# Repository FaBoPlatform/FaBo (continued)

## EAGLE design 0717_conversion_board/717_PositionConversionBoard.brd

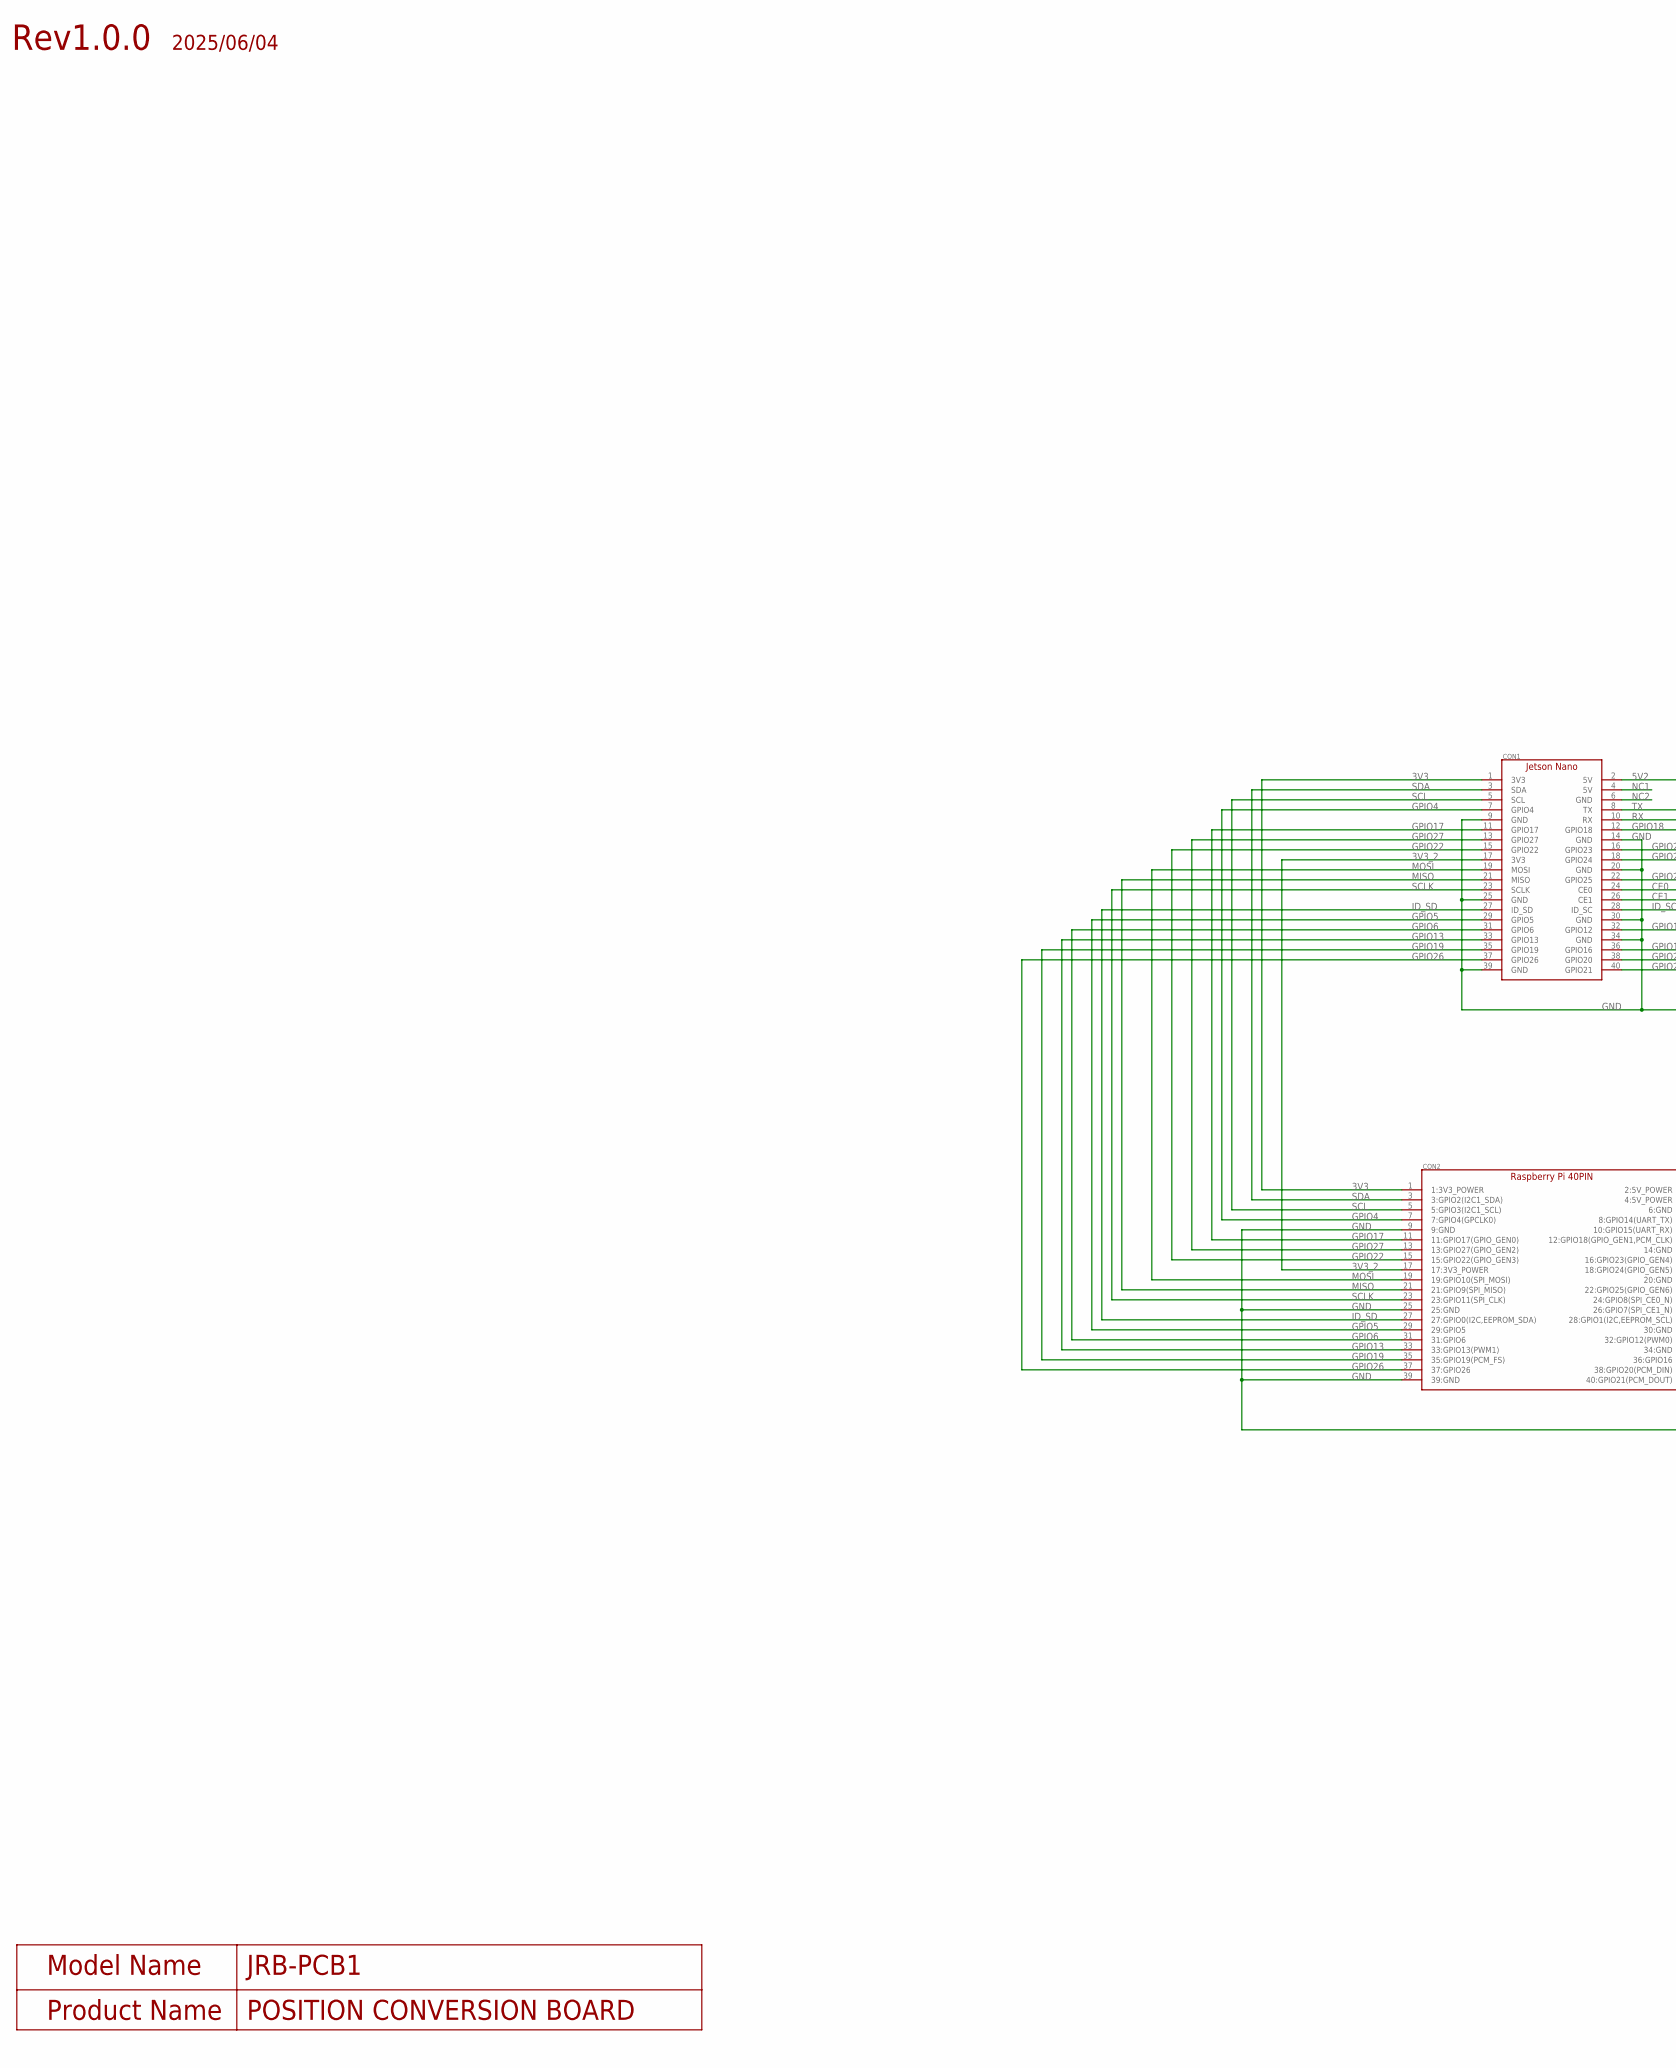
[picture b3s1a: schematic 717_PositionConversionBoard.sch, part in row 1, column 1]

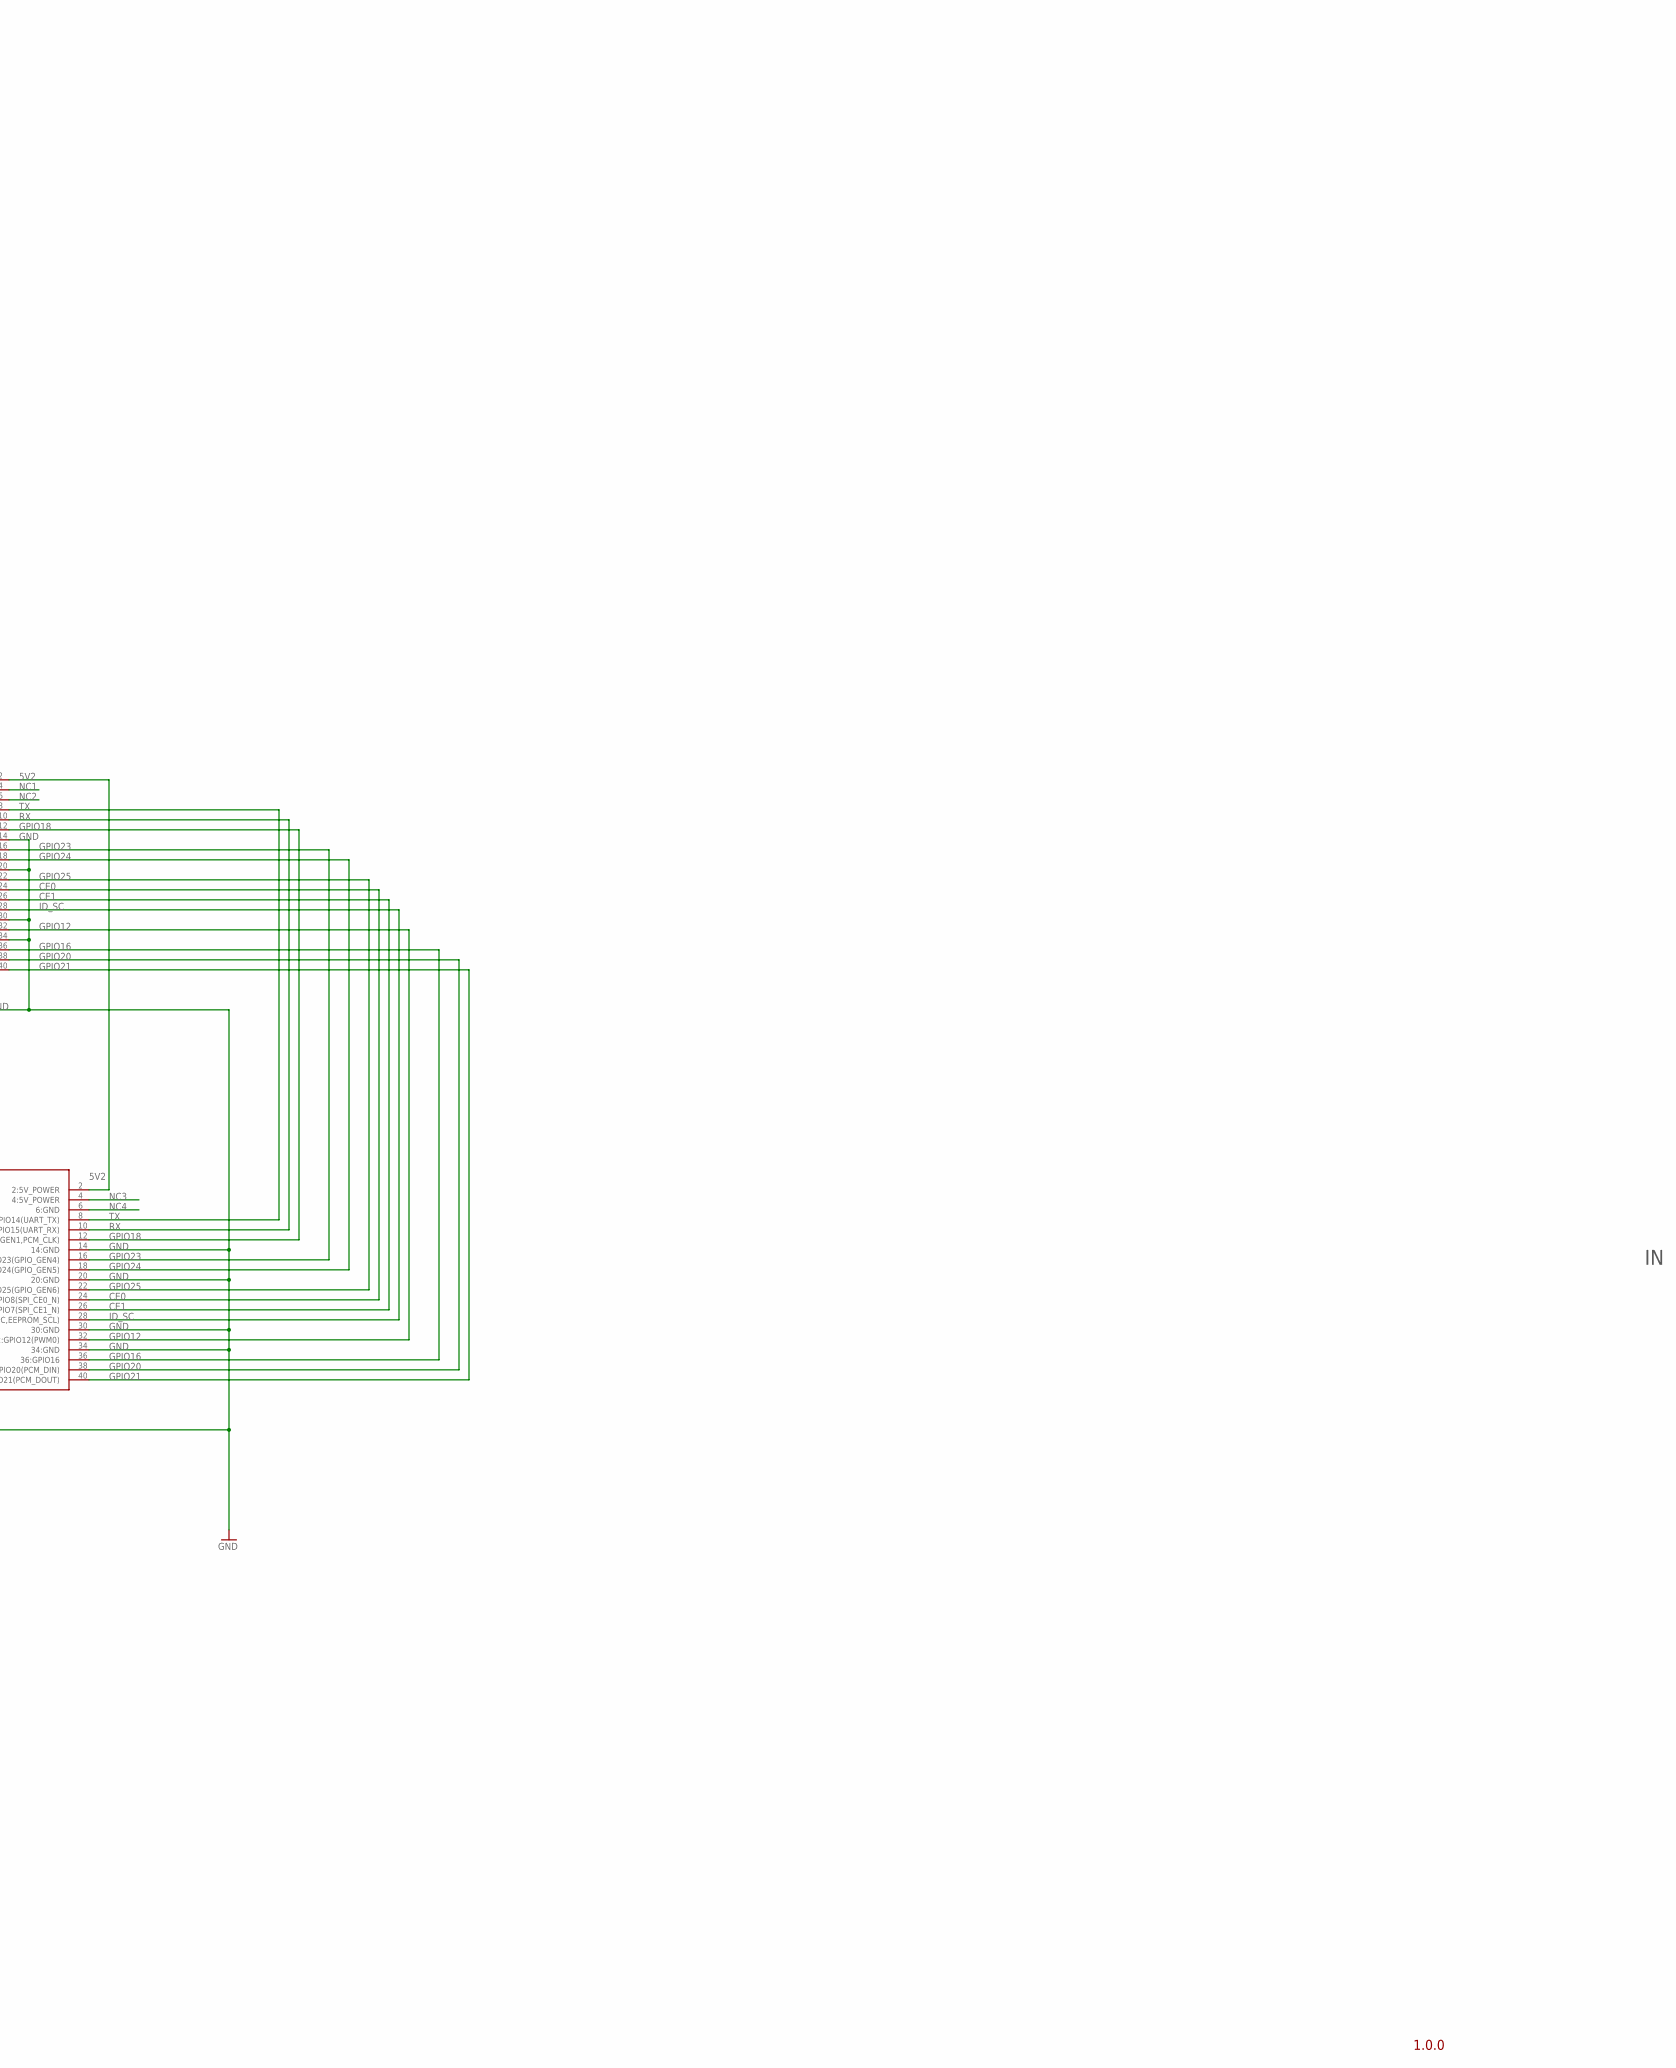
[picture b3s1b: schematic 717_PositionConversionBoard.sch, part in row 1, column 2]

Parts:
CON1: JETSON_NANOJETSON_ORIN_NANO; JETSON_ORIN_NANO_DIMENTION
CON2: RASPBERRYPI_SHEILDUPPERBOARD; RASPBERRY_PI_SHILED_NONDEMETION

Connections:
3V3: CON1.1 (3V3), CON2.1 (1:3V3_POWER)
3V3_2: CON1.17 (3V3), CON2.17 (17:3V3_POWER)
5V2: CON1.2 (5V), CON2.2 (2:5V_POWER)
CE0: CON1.24 (CE0), CON2.24 (24:GPIO8(SPI_CE0_N))
CE1: CON1.26 (CE1), CON2.26 (26:GPIO7(SPI_CE1_N))
GND: CON1.9 (GND), CON1.14 (GND), CON1.20 (GND), CON1.25 (GND), CON1.30 (GND), CON1.34 (GND), CON1.39 (GND), CON2.9 (9:GND), CON2.14 (14:GND), CON2.20 (20:GND), CON2.25 (25:GND), CON2.30 (30:GND), CON2.34 (34:GND), CON2.39 (39:GND)
GPIO4: CON1.7 (GPIO4), CON2.7 (7:GPIO4(GPCLK0))
GPIO5: CON1.29 (GPIO5), CON2.29 (29:GPIO5)
GPIO6: CON1.31 (GPIO6), CON2.31 (31:GPIO6)
GPIO12: CON1.32 (GPIO12), CON2.32 (32:GPIO12(PWM0))
GPIO13: CON1.33 (GPIO13), CON2.33 (33:GPIO13(PWM1))
GPIO16: CON1.36 (GPIO16), CON2.36 (36:GPIO16)
GPIO17: CON1.11 (GPIO17), CON2.11 (11:GPIO17(GPIO_GEN0))
GPIO18: CON1.12 (GPIO18), CON2.12 (12:GPIO18(GPIO_GEN1,PCM_CLK))
GPIO19: CON1.35 (GPIO19), CON2.35 (35:GPIO19(PCM_FS))
GPIO20: CON1.38 (GPIO20), CON2.38 (38:GPIO20(PCM_DIN))
GPIO21: CON1.40 (GPIO21), CON2.40 (40:GPIO21(PCM_DOUT))
GPIO22: CON1.15 (GPIO22), CON2.15 (15:GPIO22(GPIO_GEN3))
GPIO23: CON1.16 (GPIO23), CON2.16 (16:GPIO23(GPIO_GEN4))
GPIO24: CON1.18 (GPIO24), CON2.18 (18:GPIO24(GPIO_GEN5))
GPIO25: CON1.22 (GPIO25), CON2.22 (22:GPIO25(GPIO_GEN6))
GPIO26: CON1.37 (GPIO26), CON2.37 (37:GPIO26)
GPIO27: CON1.13 (GPIO27), CON2.13 (13:GPIO27(GPIO_GEN2))
ID_SC: CON1.28 (ID_SC), CON2.28 (28:GPIO1(I2C,EEPROM_SCL))
ID_SD: CON1.27 (ID_SD), CON2.27 (27:GPIO0(I2C,EEPROM_SDA))
MISO: CON1.21 (MISO), CON2.21 (21:GPIO9(SPI_MISO))
MOSI: CON1.19 (MOSI), CON2.19 (19:GPIO10(SPI_MOSI))
NC1: CON1.4 (5V)
NC2: CON1.6 (GND)
NC3: CON2.4 (4:5V_POWER)
NC4: CON2.6 (6:GND)
RX: CON1.10 (RX), CON2.10 (10:GPIO15(UART_RX))
SCL: CON1.5 (SCL), CON2.5 (5:GPIO3(I2C1_SCL))
SCLK: CON1.23 (SCLK), CON2.23 (23:GPIO11(SPI_CLK))
SDA: CON1.3 (SDA), CON2.3 (3:GPIO2(I2C1_SDA))
TX: CON1.8 (TX), CON2.8 (8:GPIO14(UART_TX))

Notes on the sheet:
1.0.0
Rev1.0.0
2025/06/04
Model Name
JRB-PCB1
Product Name
POSITION CONVERSION BOARD

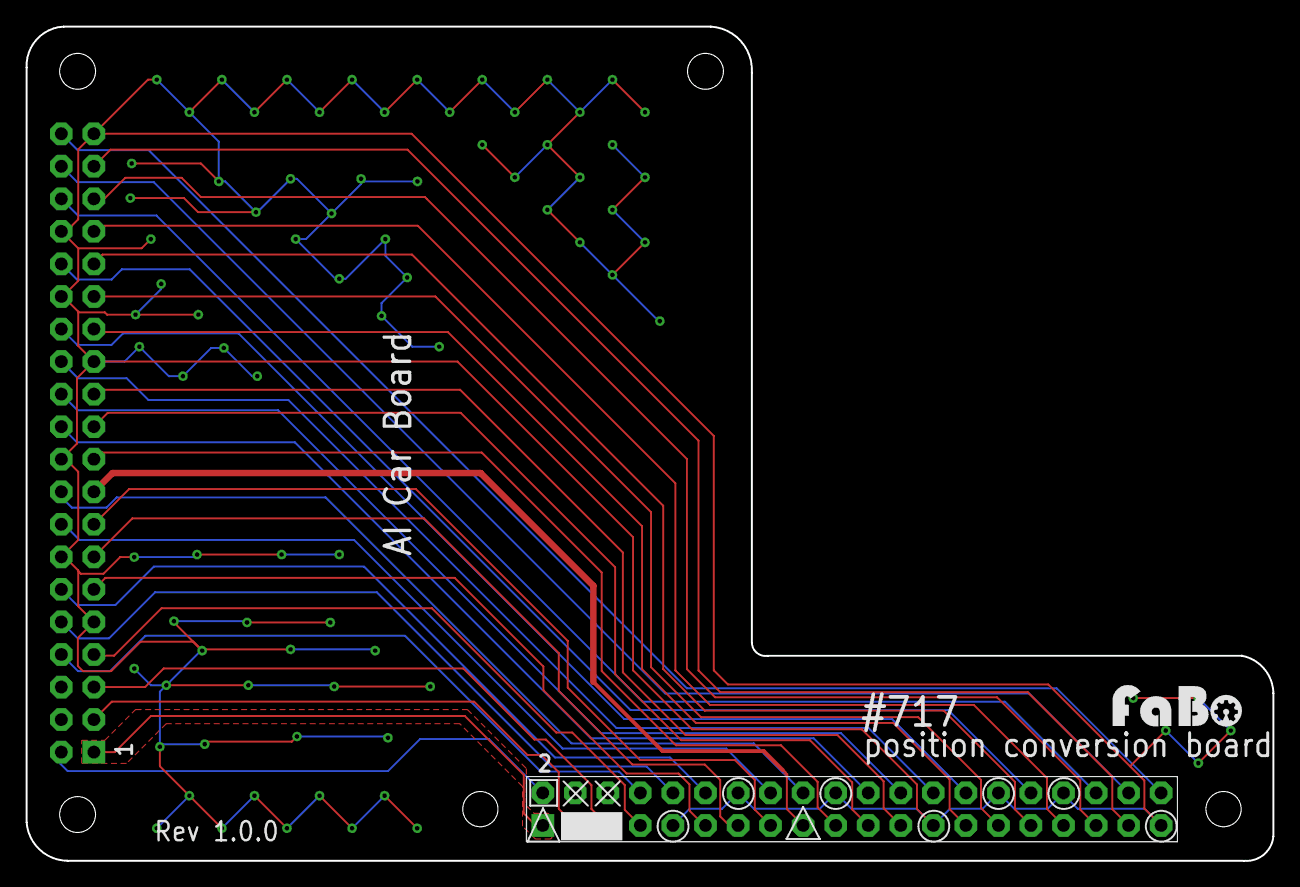
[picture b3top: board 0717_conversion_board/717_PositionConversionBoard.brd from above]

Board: 2 copper layers, 97.3 x 65.1 mm, 4 parts (1 on the bottom side), 32 nets.

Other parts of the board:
U$3, U$5: LOGO_FABO_M

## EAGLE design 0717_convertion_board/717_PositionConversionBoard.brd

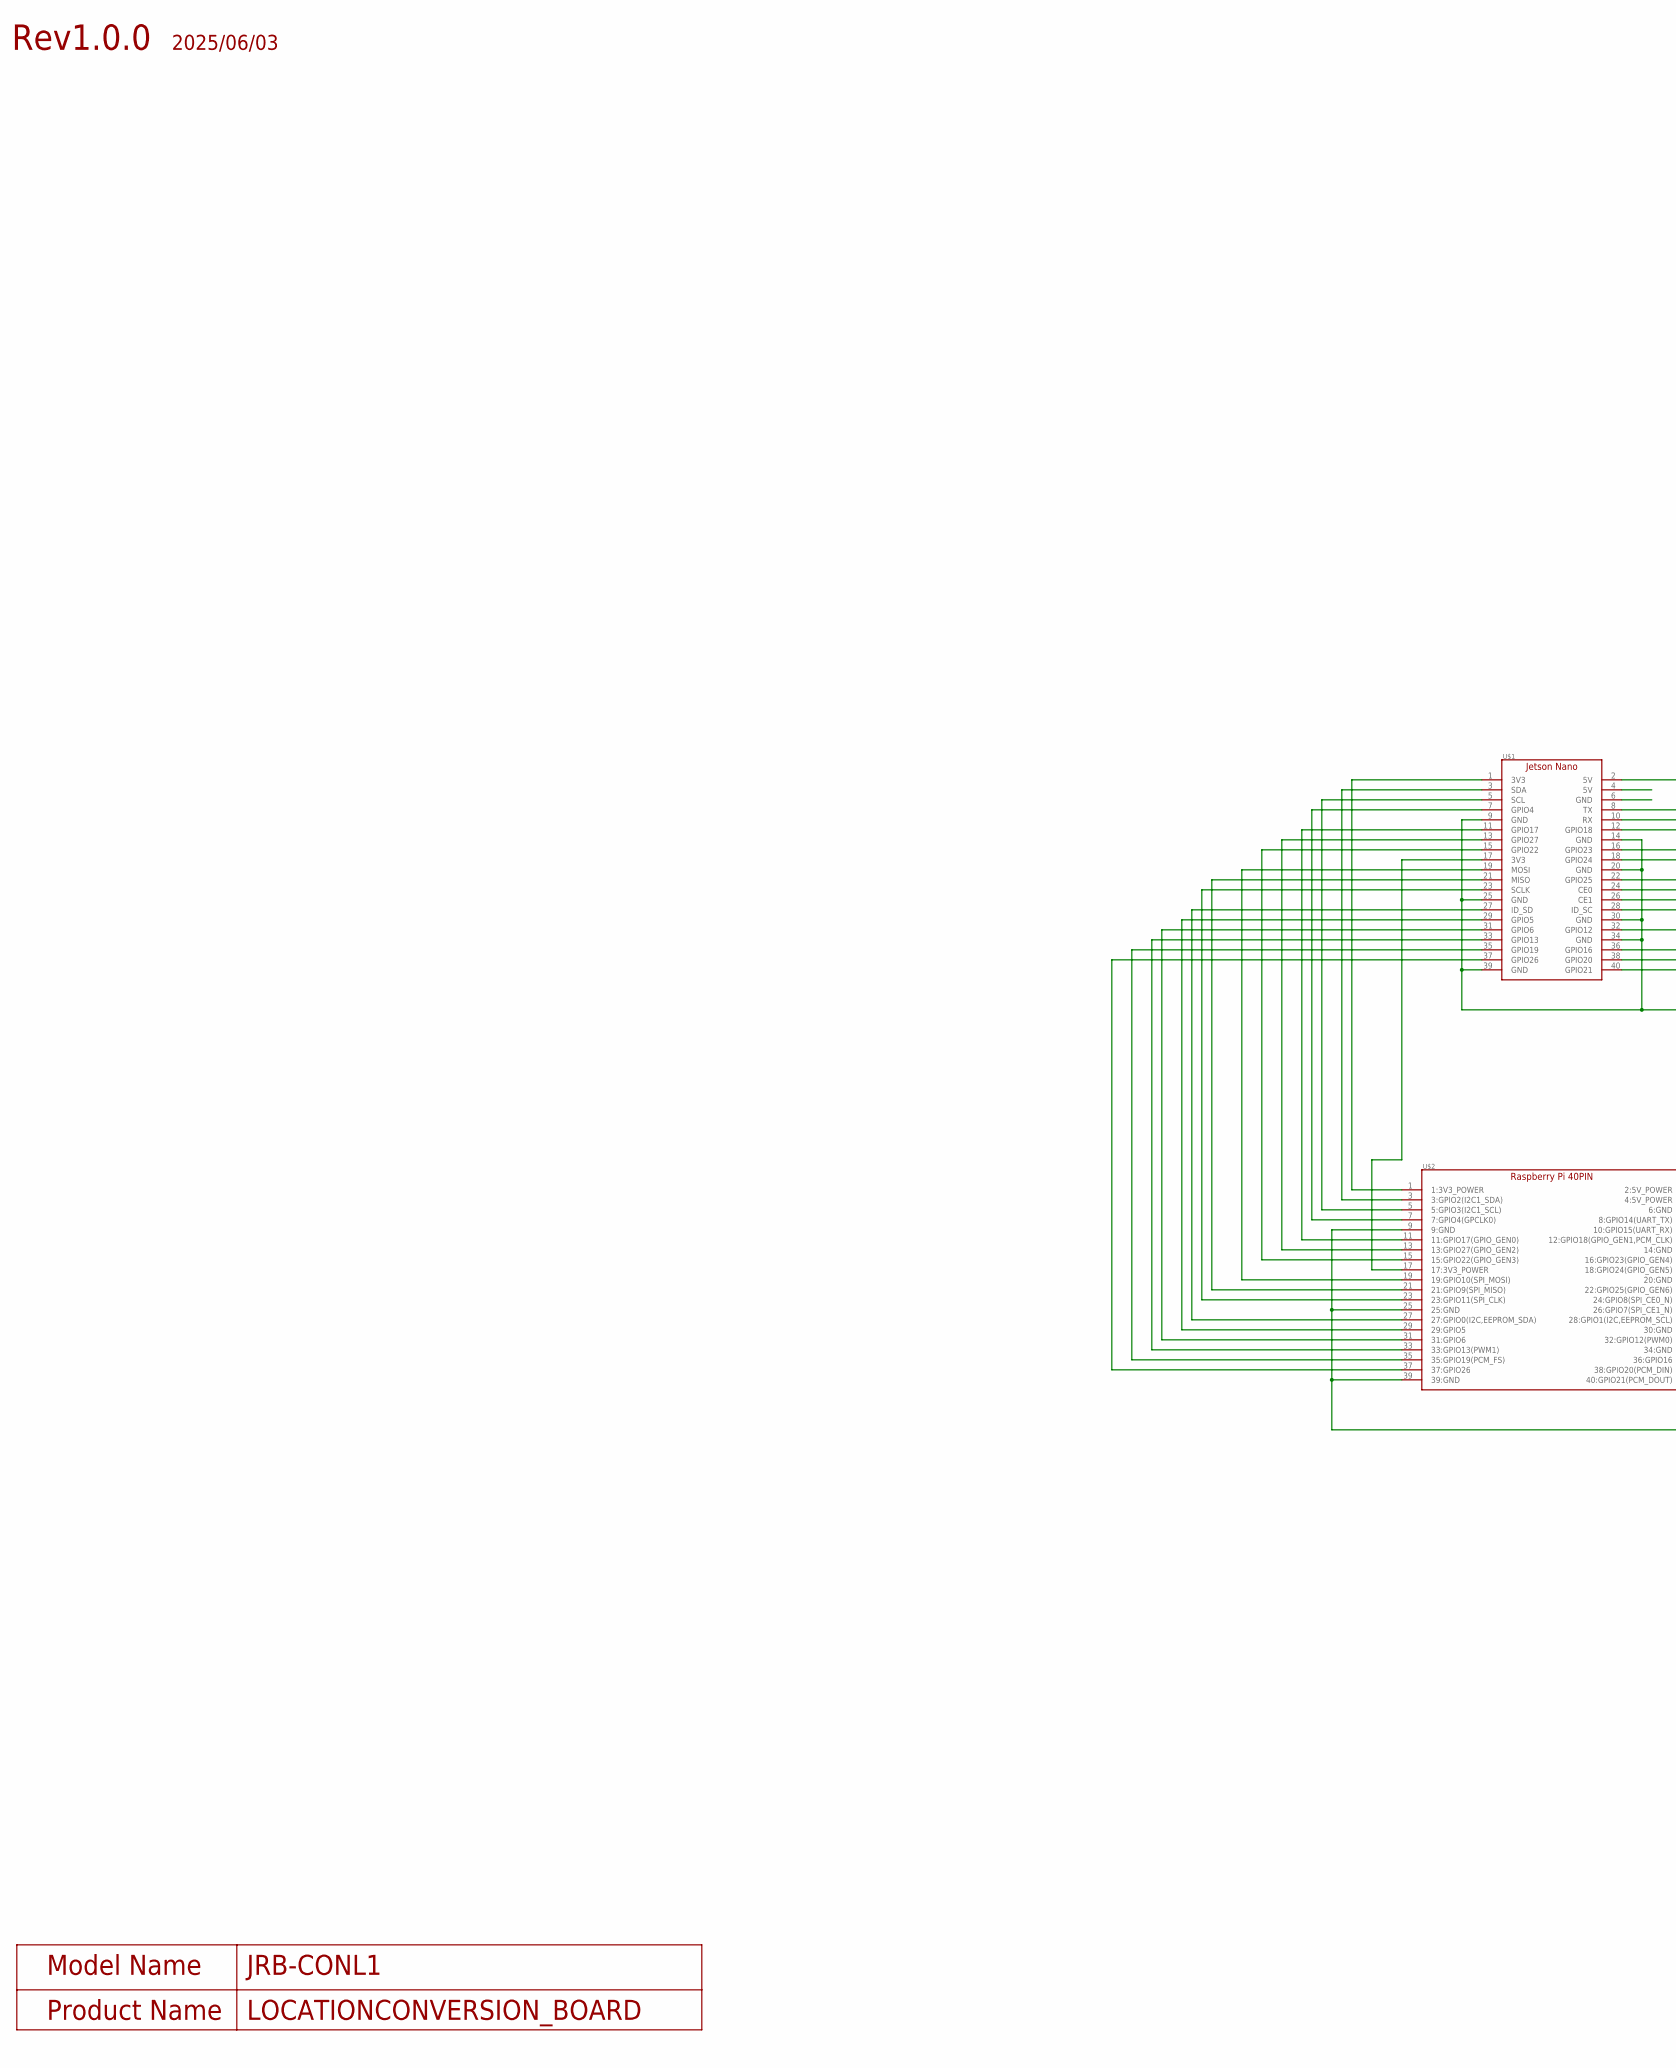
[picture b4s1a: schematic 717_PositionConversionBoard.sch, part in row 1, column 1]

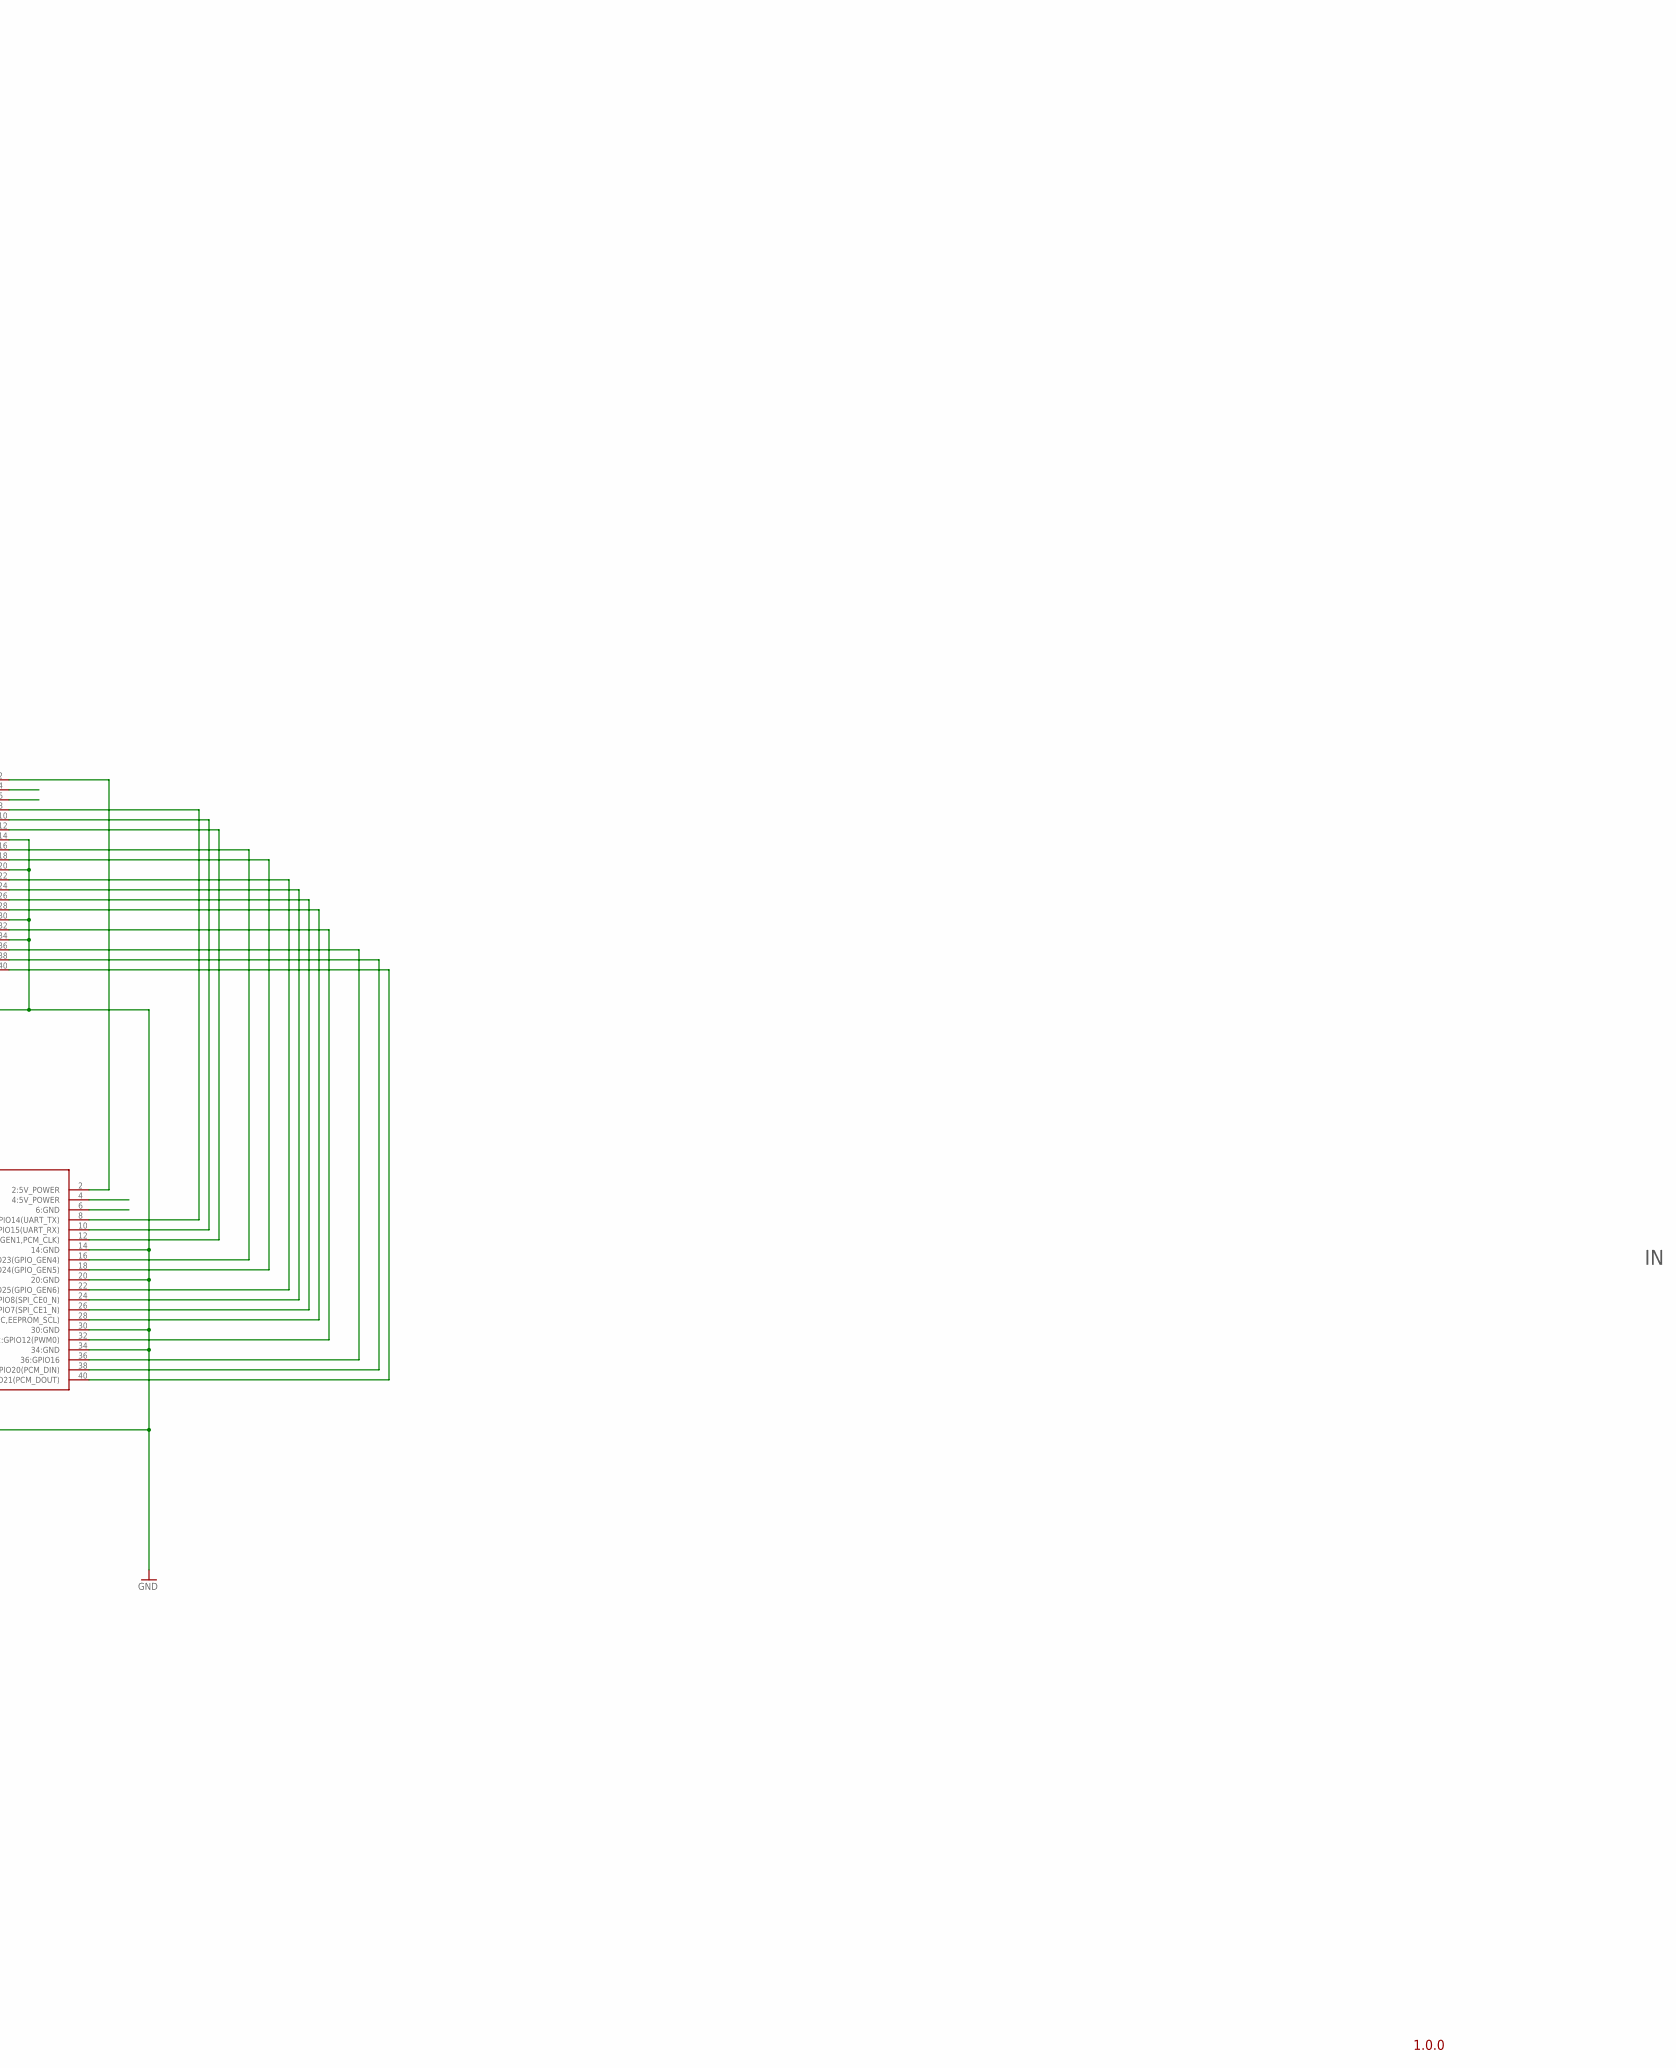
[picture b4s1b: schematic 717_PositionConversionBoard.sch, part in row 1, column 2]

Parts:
U$1: JETSON_NANOJETSON_ORIN_NANO; JETSON_ORIN_NANO_DIMENTION
U$2: RASPBERRYPI_SHEILDUPPERBOARD; RASPBERRY_PI_SHILED_NONDEMETION

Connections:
3V3: U$1.1 (3V3), U$2.1 (1:3V3_POWER)
3V3_2: U$1.17 (3V3), U$2.17 (17:3V3_POWER)
5V2: U$1.2 (5V), U$2.2 (2:5V_POWER)
GND: U$1.9 (GND), U$1.14 (GND), U$1.20 (GND), U$1.25 (GND), U$1.30 (GND), U$1.34 (GND), U$1.39 (GND), U$2.9 (9:GND), U$2.14 (14:GND), U$2.20 (20:GND), U$2.25 (25:GND), U$2.30 (30:GND), U$2.34 (34:GND), U$2.39 (39:GND)
GP15: U$1.15 (GPIO22), U$2.15 (15:GPIO22(GPIO_GEN3))
unnamed: U$1.3 (SDA), U$2.3 (3:GPIO2(I2C1_SDA))
unnamed: U$1.5 (SCL), U$2.5 (5:GPIO3(I2C1_SCL))
unnamed: U$1.7 (GPIO4), U$2.7 (7:GPIO4(GPCLK0))
unnamed: U$1.11 (GPIO17), U$2.11 (11:GPIO17(GPIO_GEN0))
unnamed: U$1.13 (GPIO27), U$2.13 (13:GPIO27(GPIO_GEN2))
unnamed: U$1.19 (MOSI), U$2.19 (19:GPIO10(SPI_MOSI))
unnamed: U$1.21 (MISO), U$2.21 (21:GPIO9(SPI_MISO))
unnamed: U$1.8 (TX), U$2.8 (8:GPIO14(UART_TX))
unnamed: U$1.23 (SCLK), U$2.23 (23:GPIO11(SPI_CLK))
unnamed: U$1.27 (ID_SD), U$2.27 (27:GPIO0(I2C,EEPROM_SDA))
unnamed: U$1.29 (GPIO5), U$2.29 (29:GPIO5)
unnamed: U$1.31 (GPIO6), U$2.31 (31:GPIO6)
unnamed: U$1.33 (GPIO13), U$2.33 (33:GPIO13(PWM1))
unnamed: U$1.35 (GPIO19), U$2.35 (35:GPIO19(PCM_FS))
unnamed: U$1.37 (GPIO26), U$2.37 (37:GPIO26)
unnamed: U$1.10 (RX), U$2.10 (10:GPIO15(UART_RX))
unnamed: U$1.12 (GPIO18), U$2.12 (12:GPIO18(GPIO_GEN1,PCM_CLK))
unnamed: U$1.16 (GPIO23), U$2.16 (16:GPIO23(GPIO_GEN4))
unnamed: U$1.18 (GPIO24), U$2.18 (18:GPIO24(GPIO_GEN5))
unnamed: U$1.22 (GPIO25), U$2.22 (22:GPIO25(GPIO_GEN6))
unnamed: U$1.24 (CE0), U$2.24 (24:GPIO8(SPI_CE0_N))
unnamed: U$1.26 (CE1), U$2.26 (26:GPIO7(SPI_CE1_N))
unnamed: U$1.28 (ID_SC), U$2.28 (28:GPIO1(I2C,EEPROM_SCL))
unnamed: U$1.32 (GPIO12), U$2.32 (32:GPIO12(PWM0))
unnamed: U$1.36 (GPIO16), U$2.36 (36:GPIO16)
unnamed: U$1.38 (GPIO20), U$2.38 (38:GPIO20(PCM_DIN))
unnamed: U$1.40 (GPIO21), U$2.40 (40:GPIO21(PCM_DOUT))
NC1: U$1.4 (5V)
NC2: U$1.6 (GND)
NC3: U$2.4 (4:5V_POWER)
NC4: U$2.6 (6:GND)

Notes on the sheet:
1.0.0
Rev1.0.0
2025/06/03
Model Name
JRB-CONL1
Product Name
LOCATIONCONVERSION_BOARD

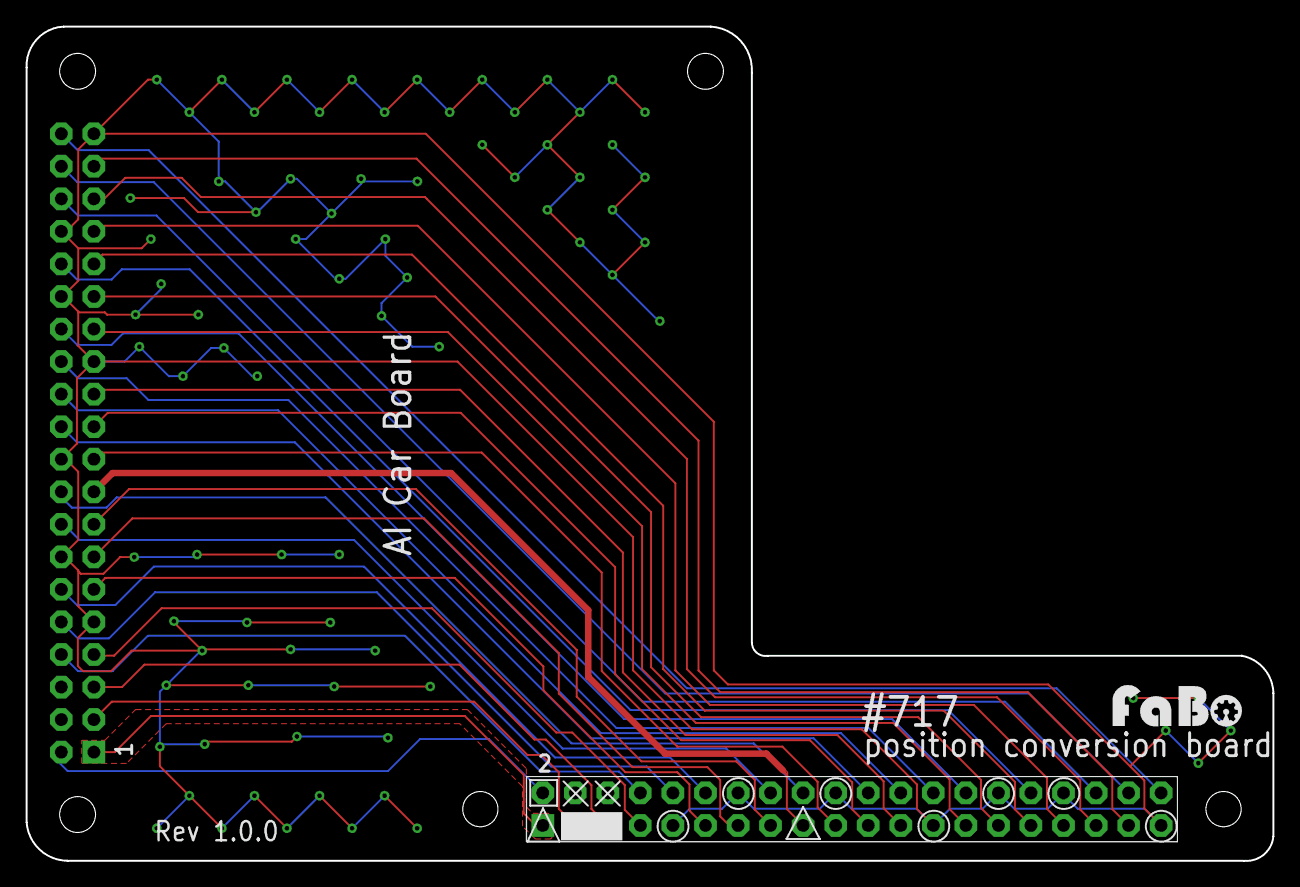
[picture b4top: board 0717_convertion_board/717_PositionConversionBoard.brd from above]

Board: 2 copper layers, 97.3 x 65.1 mm, 4 parts (1 on the bottom side), 32 nets.

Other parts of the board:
U$3, U$5: LOGO_FABO_M

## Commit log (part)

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2021-05-14 #315 gps_NEOM8U README追加
2021-05-14 #519 outin_jetson_nano README追加
2021-05-14 #510 health_arduino README修正
2021-05-14 #511 outin_things_imx7 README修正
2021-05-14 #513 lora_raspberrypi_ES920 README修正
2021-05-14 #514 lora_arduino_RAK811 README修正
2021-05-14 #517 lora_arduino_ES920 README修正
2021-05-14 #520 servo_pwm ロゴ修正
2021-05-14 #522 outin_jetson_xavier ロゴ修正
2021-05-14 #523 outin_jetbook ロゴ修正
2021-05-14 #525 kaya ロゴ修正
2021-05-14 #601 motor ロゴ修正
2021-05-14 #602 stmotor ロゴ修正
2021-05-14 #604 romwriter ロゴ修正
2021-05-14 #605 motor_rasppi ロゴ修正
2021-05-17 #606 motor_ichigojam ロゴ修正、リファイン
2021-05-17 #607 stmotor_rasppi ロゴ修正
2021-05-17 #608 donkey_205 ロゴ修正
2021-05-17 #608 donkey_nodisplay ロゴ修正
2021-05-17 #610 motor_wheel ロゴ修正
2021-05-17 #612 JetRacer ロゴ修正
2021-05-17 #613 jetbot_edu ロゴ修正
2021-05-17 #615 droracer ロゴ修正
2021-05-17 #617 jetracer_mini ロゴ修正
2021-05-17 #702 breakout_3pin ロゴ修正
2021-05-17 #703 breakout_i2c ロゴ修正
2021-05-17 #705 breakout_3pin_2mm ロゴ修正
2021-05-17 #706 breakout_i2c_2mm ロゴ修正
2021-05-17 #708 universal_3pin ロゴ修正
2021-05-17 #710 universal_serial ロゴ修正
2021-05-17 #712 universal_i2c_long ロゴ修正
2021-05-18 #714 breakout_arduino_spi ロゴ修正
2021-05-18 #715 repeater_i2c ロゴ修正
2021-05-18 #801 ibeacon_type1 ロゴ修正
2021-05-18 #803 ibeacon_type3 ロゴ修正
2021-05-18 #802 ibeacon_type2 ロゴ修正
2021-05-18 #901 module-USBserial ロゴ修正、リファイン
2021-05-18 #1601 board_firmata ロゴ修正
2021-05-18 #1604 lora_rak811_usb ロゴ修正
2021-05-18 #1605 lora_ES920_usb ロゴ修正
2021-05-18 #1607 426mhz_module ロゴ修正
2021-05-18 #2002 currentmeasure ロゴ修正
2021-05-19 #2004 converter_jl2tc ロゴ修正
2021-05-19 #3001 voltera_i2c ロゴ修正
2021-05-19 #3002 voltera_serial ロゴ修正
2021-05-19 #3003 voltera_3pin ロゴ修正
2021-05-19 #3005 voltera_beacon ロゴ修正
2021-05-25 EAGLE初期設定スクリプト追加
2021-05-25 EAGLE初期設定スクリプト修正
2021-06-02 OUT/IN for Raspberry Pi Pico(Rev.Beta1) 追加
2021-06-03 アナログ用電源ピンを変更
2021-06-07 #405 led_jetracer バージョンナンバー更新漏れ修正
2021-06-08 #406 led_jetracer_matrix リファイン
2021-06-10 #519 Jetson OUTIN DCプラグ変更、GPIO27信号切り替え追加、アナログADC電源を3.3Vに変更。
2021-06-11 #519 Jetson Nano OUTIN SPIコネクタの変更。
2021-07-01 #612 JetRacer Rev12 新回路アップデート
2021-07-07 #452 Speaker Rev101 2mm ジャンパスイッチ追加
2021-07-08 #519 Jetson OUT/IN Rev15 PWM8出力、外部電源廃止、3.3V低ノイズ電源,#452 表示間違い訂正。
2021-07-10 #452 Spreaker スピーカー出力フィルター追加
2021-07-12 #519 jetson outin
2021-07-12 #519 Jetson Nano シルク印刷位置修正、PWMピン位置修正
2021-07-12 #304 usb serial レベルシフトIC変更
2021-07-14 #452 Speaker ソルダーマスク問題対処
2021-07-15 #452 Speaker 放熱パターン削除
2021-07-19 #127 Microphone type J Rev102A追加
2021-08-06 #612 JetRacer 極小とりやめ修正
2021-08-21 JetRacer Wifi支持パーツナット避け対策済みRev4
2021-09-03 #519 Jetson Nano OUTIN Rev１６ インターフェース配置変更
2021-09-06 #519 Jetson Nano Edge AI Kit Rev16 シルク位置、GND強化
2021-09-08 JetBot WifiAnntena部品 穴調整5.7mm->5.8mm
2021-09-08 #612 JetRacer ファイルリネーム,シルク追加位置修正、GNDビア追加
2021-09-10 #611 JetBot Controller Board Update OLEDコネクタのピンビッチランド間拡大、ランド縮小、直角配線修正、OLEDインターフェース設定回路の修正（抵抗追加1個）
2021-10-16 JetsonNano519 アナログ電源回路修正
2021-10-27 #612 JetRacer PCA9685 OEとボタンを追加
2021-10-30 #612 JetRacer Rev2.0.15追加 MOS-FET変更、絶縁化
2021-11-01 #615 DroRacerの配線修正、エラー修正
2021-11-15 #526 Rapsberry pi pico out/in アナログポート５V化、I2Cレベル変換追加
2021-11-15 #612 JetRacer Rev3.0.0 MCUを328PからRaspberrypi Picoへ変更
2021-11-17 JetRacer4本対応アンテナ支持Rev１（ナロー版、ワイド版）
2021-11-19 #612 JetRacer Pico版の修正 プルダウン抵抗の追加 GND修正
2021-11-22 #612 JetRacer 抵抗定数の変更 R33,R34,R43,R44 220->330
2021-12-06 #526 Raspberry Pi Pico ボードアップデート REV1.0.2 BRICKへの電源を選択性に。コネクタは両サイドへ変更（トップからサイド）、表記はDからGPへ変更。
2022-01-11 #452 Speaker Rev102追加 ４６サイズに変更、スピーカーラインにLCローパスフィルター追加、通信ラインはRCフィルター追加、オーディオ用OSコンデンサ、フィルムコンデンサを追加。
2022-01-13 #452 Speaker OSコン間隔拡大、ネジ穴位置修正、ビアの数増量、I2Sにフィルターを追加。
2022-01-14 #304 USB Serial スリーステートバッファーの変更 電圧対応
2022-02-19 #612 JetRacer Rev2.0.17 追加、車高が低い車にも対応。OLEDを分離。
2022-02-20 612 JetRacer Rev2.0.17 シルク追加、形状の修正
2022-02-20 JetRacer WIFi 支持パーツ Rev６ 新しいモデルに対応 F社GT4
2022-02-24 612ローボディ用追加ボード
2022-03-05 #452 Speaker シルク番号の間違いを修正。
2022-03-05 #214 OLED For JetRacer 新バージョン追加
2022-03-07 #214,#405 寸法記入、ファイル名変更
2022-03-13 #612 Rev2.0.18 B トランジスタ抵抗干渉修正、定位数変更 R30 221,R25 221 ,R28 103へ変更。
2022-03-25 Rev2.0.19追加
2022-03-27 612 JetRacer ハードウェア割り込みピン修正
2022-04-18 #611 JetBot Controller Board Rev1.2.8追加 PCA9685BS
2022-04-19 #612 JetRacer ３２８P割り込みピン最適化、コネクタ部分表記、レベル変換代替え品対応、信号処理3.3V駆動化
2022-06-01 #611 JetBot PCA9685i2cアドレス設定の修正
2022-06-03 Add counter shield.
2022-06-03 Add switcher can.
2022-06-03 JetRacer 新ファームウェア追加 Rev2.0.21向け
2022-06-04 #612 JetRacer Rev2.0.21配線修正
2022-06-07 #245 Gas Detection BME688採用ガス検知センサー追加
2022-06-10 #527 AI BLOCKS追加 Rev1.0.0 alpha
2022-06-11 #527 FaBoBlocks名称変更、Brickピン間違い修正、P0のアサインを変更
2022-06-25 #612 JetRacer Rev2.0.21 Firmware V3.1 追加
2022-06-27 #526 AI BLOCKS FULL SIZE追加
2022-06-29 #311 LoRaWan FaBo Brocks Rev2.0.0追加
2022-06-29 #311 LORAWAN Brick シンボル違いを修正。
2022-07-08 R28 104から472に抵抗を変更。
2022-07-12 #311 LORA ES920LR Rev2.0.1 TX,RX線入れ替え
2022-07-15 #526 FaBo Blocks Rev2.0.1追加 インレット電源追加。
2022-07-19 #0129 Ultrasound 超音波センサー、#450 PDMマイク、#528 Wioシールド追加
2022-07-19 #245 gas deticition BME688 基板形状の変更、寸法の追加、#311 Lora エラー修正、#528 Wio terminal on ES920LR追加。
2022-07-30 #130 Pad追加
2022-07-30 #102 BUZZER FaBo Blocks 追加
2022-08-02 #519 Jetson Nano FaBo Blocks 2GB 追加 Rev2.0.0
2022-08-02 #246 PWM(PCA9685) Rev2.0.0 新規追加
2022-08-02 #129 Ultrasound RJ 11のコネクタ位置変更
2022-08-02 #351 2.8inchLCDの追加。
2022-08-07 #311 LoRa BLOCKS Rev2.0.2 RESET回路の修正、UARTプルアップ
2022-08-09 #457 I2S Stereo Sound エラー修正、シルク間違い修正
2022-08-10 #304 USB Serial USB FaBo BLOCKS 追加
2022-08-15 #246_PWM Rev2.0.1 電解コンデンサー追加
2022-08-15 #311 LoRaWAN ES920LR 修正リセット回路にデジトラ追加
2022-08-16 #1606 LoRa Module Rev1.0.3 フットプリント修正
2022-08-18 #311 LoRa ES920 Rev2.0.2 モジュールDIP化
2022-08-29 #351 A/Dコンバーター 基板サイズーブロック幅微調整
2022-08-29 #246 PWM(PCA9685) 電解コンデンサ追加、外部発振追加、I2Cアドレス設定の変更
2022-08-29 #350 2.8inchLCD MOS I ,MISOピン入れ替え
2022-08-30 #519 JetsonNano Rev2.0.1 SPI-LED,I2C,SPIポート追加 4GBモデル対応
2022-08-30 #246 PWM ロゴを大きなものに変更。
2022-08-30 #102 Buzzer メーカーロゴ整列
2022-08-31 #350 2.8inchLCD コネクタ名称追加
2022-09-09 #405 JetRacer LED Rev2.0.2 I2Cポート増設、LED上方、下方
2022-09-15 #612 JetRacer Rev2.0.21 10K->0に変更。
2022-09-20 #526 RasberryPi Fabo Blocks アップデートRev2.0.2
2022-09-29 #612 JetRacer Rev2.0.21 実装部品の注釈追加。
2022-10-21 pico用outinボード
2022-10-21 LoRa Communicator
2022-10-21 Jetracerを1個のLEDを追加
2022-11-09 #612 JetRacer Rev2.0.22 R49,50,51,52 350から390へ抵抗定数変更
2022-11-09 #408 Jetracer_appendboard回路図追加
2022-11-14 #612 JetRacer Rev2.0.24 Rev2.0.21の修正 低電圧対策済み
2022-11-15 #408 JetRacer ApendBoard SPIコネクタの変更
2022-11-17 #612 JetRacer Rev2.0.24 バイパス回路追加
2022-11-17 #408 JetRacer LED AppendBoard 試作品
2022-12-14 #612 JetRacer Rev2.0.23 抵抗の定数変更 R15,16 を4.7Kから1.8Kへ変更いたしました。
2022-12-14 #612 JetRacer ファームウェアバグフィックス
2022-12-16 #612 JetRacer ファームウェア v3.3全てのモデルに対してチャッタリング対策追加
2022-12-26 #611 JetBot Rev1.2.9追加 PCA9685PW用、ピンソケット追加
2022-12-26 #612 JetRacerRev2.0.25追加
2022-12-27 #612 JetRacerアップデート 基板形状縮小、スライドスイッチの変更、ブリーダー抵抗追加。
2022-12-28 #612 JetRacer Rev2.0.25 ベタパターン修正、抵抗定数の変更
2023-01-06 #408 LED JetRacer ApendBorad test Firmware 追加
2023-01-12 #304 USB Serial Rev2.0.1 基板縮小
2023-01-20 #214 OLED の版数番号の変更 ブリッジ防止
2023-02-02 #526 FaBo Blocks for Raspberry pico Rev2.0.3 Arduino Picoのピン変更
2023-02-02 #526 FaBo Blocks Rev2.0.3 表示間違い修正
2023-02-10 #103 BUTTON Rev2.0.0 追加
2023-02-10 #103 BUTTON Rev2.0.0 シルク追加
2023-02-17 #408 JetRacer LED Board RP2040に変更。
2023-02-24 #350 LCD 信号混合、等長配線
2023-02-27 #350 LCD-SPI ピン表示シルク追加。
2023-02-28 #350 SPI-LCD シルク印刷部分修正
2023-03-07 #612 JetRacer Controller Board 定数表記位置補正（表）
2023-03-07 #612 JetRacer Controller Board 定数表記位置補正（裏）、Revision表記違い修正
2023-03-08 #612 JetRacer Rev2.0.28 Firmware 定数変更
2023-03-10 #612 JetRacer Rev2.0.28 定数の変更 ゲート抵抗４７１に変更。リセット信号コンデンサなし、３２８Pの１０６のコンデンサなし。
2023-04-04 #457 Stereo Sound Speaker マイク削除
2023-04-05 #454 Stereo Microphone FaBo Blocks化 新規Rev2.0.0
2023-04-05 #454,#457 ピンアサインロゴ、シルク追加。
2023-04-06 #519 Jetson outin SPI,I2S等長配線
2023-04-12 #529 Agent Kit Rev1.3 アップ
2023-05-31 #454 stereo_mic Rev2.0.1へアップデート ロゴ追加、文字書体変更。
2023-06-09 FaBo KeyBoardサンプル４キー版追加
2023-07-27 #612 JetRacer FWをアップデートV3.6 Rev2.0.17のモード切り替えスイッチを有効化
2023-07-31 #519 Jetson Nano FaBo Blocks Argent Kit Rev2.1.0
2023-08-01 #519 Jetso nano Rev2.1.0 修正リリースアップデート
2023-08-09 #612 JetRacer Rev2.0.30 追加コントロール基板 OLED一体型後方整形 Gecko Car対応
2023-08-10 #612 JetRacer Rev2.0.30 リリースアップデート
2023-08-28 #612 JetRacer Control Board ファームウェアアップデート V3.7 切り替えノイズ対策追加
2023-08-30 #612 JetRacerファームウェアアップデート プロポレスモード削除
2023-09-06 #612 JetRacer Rev3.0.0 コネクタ仕切り線追加
2023-09-06 #612 JetRacer Controller Board Firmware ESP32C3用追加。
2023-09-15 #612 JetRacer ESP32-S3に変更、IMUを追加、LED外灯追加
2023-09-18 #612 JetRacer Rev3.1.0 マルチプレクサ入力閾値によるレベル変換回路、スリーステートバッファを追加。
2023-09-19 #202 9Axis AIカー向けIMUセンサー追加。
2023-09-20 #612 JetRacer 部品位置修正
2023-09-21 #612 JetRacer Rev3.1.0 23Spec レース用コントローラー基板 ５chマルチチャンネル入力
2023-10-13 #611 JetBot Controller Board アップデート OLED穴修正、PCA 9685BSからPCA 9685PWへ変更。
2023-10-23 #612 Jetracerコントロールボード Rev3.0.1,Rev2.0.31を追加。
2023-11-07 #612 JetRacer Controller Board Rev2.0.32 328Pの駆動電圧を5Vに変更
2023-11-21 切り替え信号スワップ
2023-12-18 #612 Jetracer Rev3.0.2ディレクトリ変更
2023-12-20 #612 JetRacer Rev3.0.2 SPI LEDにジャンパー線を追加
2023-12-21 #612 JetRacer コントロール基板Xaio nRF52840 SENSEファームウェアの追加
2023-12-21 #612 JetRacer コントロール基板Xaio nRF52840 SENSEファームウェアの修正 動作確認用 ６軸コード追加
2023-12-25 #612 Jetracer コントロール基板 XIAO S3 ファームウェア回復
2024-01-13 #612 JetRacer Rev3.0.3 ディスチャージ抵抗追加２
2024-01-14 #612 JetRacer Rev3.0.3 アップデート Xiao 5V電源入力
2024-01-19 JetRacerコントロール基板Xaio ESP32S3ファームウェアRev 1.0.0追加
2024-02-01 #612 JetRacer コントロール基板 Rev3.0.3 コンデンサー電荷残留対策、カラーLED信号レベルTTL化、３．３VのLDOを追加。
2024-02-07 #405 led_jetracer Rev1.0.2 LEDの数を７個から３個へ削減、増設ポート追加
2024-02-19 #405 LED Jetracer ティアドロップの修正
2024-02-19 #612 Jetracer ベタ修正。
2024-02-20 #612 Jetracerコントロール基板 シルク印刷追加、修正 GPIO13→GP13、Not Connectを追加。
2024-02-22 #612 JetRacer Rev3.0.3 ファームウェア Version1.0.1 I2Cの不具合修正追加 起動時にディレイ
2024-02-23 #612 Jetracer esp32s3 ファームウェアIDを１に変更
2024-02-27 #612 JetRacer ESP32S3ファームウェア Version1.1.0α版追加。
2024-03-01 #612 Jetracer ファームウェア Version1.1.0 説明文修正
2024-03-04 #612 JetRacer Rev3.0.3 XIAOのUSB電源はJetson５Vから電源を引き込むので図面変 更 3.3Vの部品未実装部分追記変更 クロスマークで表記
2024-03-28 #612 JetRacer Rev3 FW XAIO ESP32S3 チャッタリング対策を回数から時間へ変更。
2024-05-28 #608 donkey board Rev3.0.0 メジャーアップデート 超音波センサー接続、BNO０５５接続
2024-06-05 JetRacer基板アップデートRev3.0.4 ブラシレスモーターセンサー信号検出、フュージョンセンサー追加BNO055
2024-06-06 #JetRacer Rev3.0.4 配線とビアが近いため修正。
2024-06-18 #612 JetRacer Rev3.0.4 ブラシレスモーターセンサー信号取得、BNO055オプション設定追加。
2024-07-03 #612 JetRacer Jetson側検査用コード追加
2024-07-03 #612 JetRacer Rev3.0.5 基板専用ファームウェア ESP32S3-DevkitC-1追加
2024-07-07 #612 JetRacer Revision3.0.5 修正 オープンドレインIC追加。I2SコネクタをDIN,DOUT用のGNDを追加。
2024-07-08 PCA9685信号線にバッファICを追加。
2024-07-09 #612 JetRacerコントローラー基板 Rev3.0.5 SPIにプルアップ抵抗追加。
2024-07-18 #612 JetRacer コントロールボード I2S等長配線実施、LED電流制限抵抗サイズ変更
2024-07-30 #612 JetRacerコントロールボード Rev3.0.6 BNO055の製造打ち切りに伴いBNO085に変更。
2024-10-29 #612 JetRacerコントロールボード Jetson Orin Nano 専用化、Jetson Nano穴廃止。
2024-11-01 #608 Donkey Board Rev3.1.1分圧抵抗定数の抵抗精度削除。
2024-11-06 #612 JetRacer Rev3.0.8 実装図アップデート メス型サーボコネクタ対応、ボード長縮小
2024-11-07 #612 JetRacer Rev3.0.8 実装図アップデート
2024-11-08 #612 JetRacer Rev3.0.8 基板サイズ修正、誤記修正。
2024-11-08 #612 JetRacer Rev3.0.8 実装図 配線最適化、サイズ調整、シルク調整
2024-11-18 #612 JetRacer Rev3.0.9 アップデート Rev3.0.3マルチプレクサ電源衝突修正
2024-11-20 #612 JetRacerRev3.0.8 BEC電源断線修正
2024-11-20 #612 JetRacer コントロール基板 Rev3.0.8,Rev3.0.9 追加修正箇所注釈追加。
2024-11-20 #612 JetRacer Rev3.0.8,Rev3.0.9配線ラベル修正。
2024-11-29 JetRacer Rev3.0.8 PCA9685 OEラインシンボル間違い修正しました。
2024-12-12 #612 JetRacerコントロール基板Rev3 Firmwareアップデート Rev1.1.5 ベータ版 pin設定をトップで実行に変更。
2024-12-14 #612 JetRacerコントロールボード Rev3.0.8 R 34,35 定数の変更 51Ωから100Ω
2025-01-31 #612 JetRacer Rev3.0.11 量産版のためコネクタ変更。
2025-02-04 #612 JetRacer Rev3.0,11 エラー修正
2025-02-20 #608 FaBo AI Board Rev3.2.0 アルファ版
2025-03-31 AI Car Board テスト治具 Rev1.0.0 アルファ版 完成
2025-04-02 AI Car Board べた修正。
2025-05-19 #608 AI Car Board Inspection Board Rev1.0.1 C34コンデンサ47uF追加、発振器マーキングポイント追加、アナログ系の電源の定数を変更、レベル変換A側電源断線修正
2025-05-27 #608 AIカーボード検査治具 Rev1.0.1アップデート
2025-06-03 #608 AICarBoard Revision3.1.2誤字修正
2025-06-03 #717 PositionConversionBoard Rev1.0.0 RaspberryPi変換基板
2025-06-04 608 AI Car Board 検査治具FWRev1.0.0リリース
2025-06-05 #608 AI Car Board検査治具アップデート ダイオード追加
2025-07-13 #608 DKFA-05 Jetson GPIOカメラピン設定を追加に伴うDTCファイル修正
2025-07-14 #608 dtsファイルに間違ったコメントアウトのプルアップ表記を修正
2025-07-14 #608 JetsonGPIO 一部のファイルだけをダウンロードするようにGitコマンドを追記。
2025-07-14 READMEコマンド追記
2025-07-14 AI Car Board Jetson.GPIO 概要説明文を追記
2025-07-14 誤字脱字修正

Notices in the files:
parts and their libraries:
FaBo-Logo: Released under the Creative Commons Attribution-ShareAlike 4.0 License
https://creativecommons.org/licenses/by-sa/4.0
